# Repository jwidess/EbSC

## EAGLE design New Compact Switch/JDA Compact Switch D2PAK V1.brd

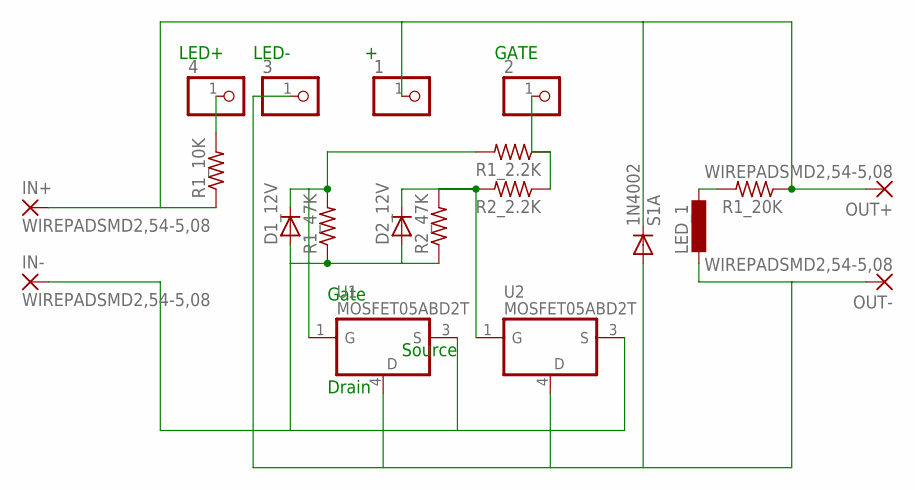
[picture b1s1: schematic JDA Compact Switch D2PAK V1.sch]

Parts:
1, 2, 3, 4: PINHD-1X1; 1X01
1N4002: S1A; DO214AC
D1_12V, D2_12V: D-SOD-80; SOD80
IN+: WIREPADSMD2,54-5,08; SMD2,54-5,08
IN-: WIREPADSMD2,54-5,08; SMD2,54-5,08
LED_1: L-EUL0805; L0805
OUT+: WIREPADSMD2,54-5,08; SMD2,54-5,08
OUT-: WIREPADSMD2,54-5,08; SMD2,54-5,08
R1_2.2K, R1_10K, R1_47K, R2_2.2K, R2_47K: R-US_M1206; M1206
R1_20K: R-US_R1206; R1206
U1, U2: MOSFET05ABD2T; D2PAK-3

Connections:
unnamed: LED_1.1, R1_20K.2
unnamed: 4.1, R1_10K.2
unnamed: D2_12V.C, R2_2.2K.2, R2_47K.2, U2.1 (G)
unnamed: 1.1, 1N4002.C, IN+.1, OUT+.1, R1_10K.1, R1_20K.1
unnamed: 2.1, R1_2.2K.1, R2_2.2K.1
unnamed: D1_12V.C, R1_2.2K.2, R1_47K.2, U1.1 (G)
unnamed: 1N4002.A, 3.1, LED_1.2, OUT-.1, U1.4 (GND), U2.4 (GND)
S: D1_12V.A, D2_12V.A, IN-.1, R1_47K.1, R2_47K.1, U1.3 (S), U2.3 (S)

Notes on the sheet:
Gate
Source
Drain
LED+
LED-
GATE

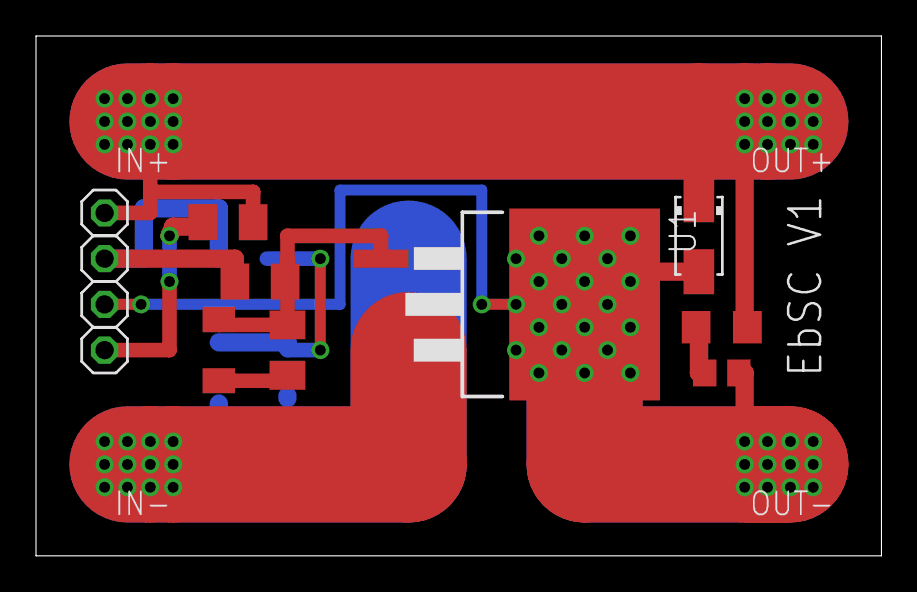
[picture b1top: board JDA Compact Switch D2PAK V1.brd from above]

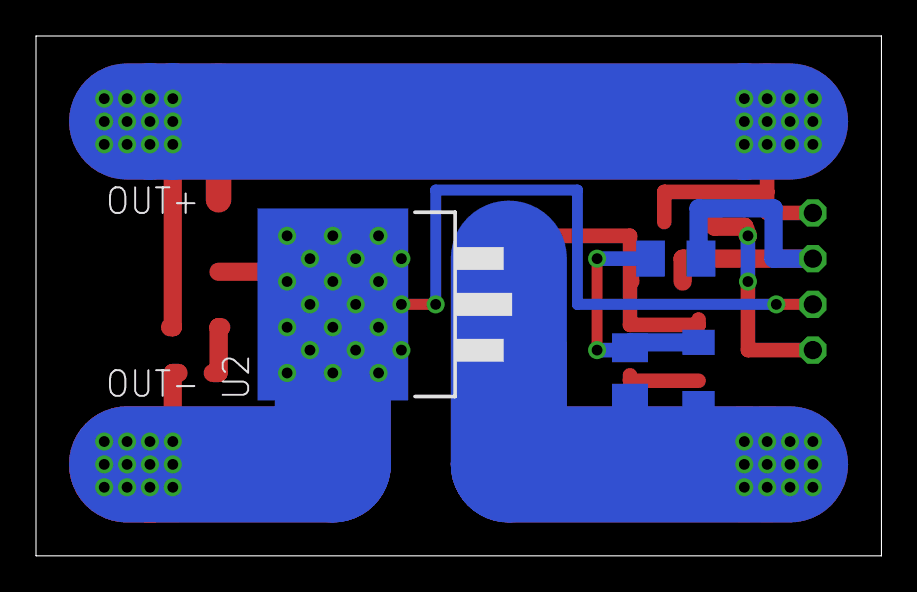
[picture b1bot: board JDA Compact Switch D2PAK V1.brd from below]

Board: 2 copper layers, 47.0 x 28.9 mm, 20 parts (4 on the bottom side), 8 nets.

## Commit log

2017-08-24 Compact Switch Files
2017-08-24 MOSFET Switch Files
